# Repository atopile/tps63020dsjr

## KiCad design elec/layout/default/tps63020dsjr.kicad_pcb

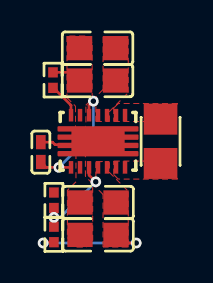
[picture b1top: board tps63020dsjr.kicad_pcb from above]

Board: 2 copper layers, 10 parts (0 on the bottom side), 8 nets.

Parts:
C1, C2, C3, C4: 10µF ±10% 25V X5R; C0805-3b2e55
C5: 100nF ±10% 16V X7R; C0402-b3ef17
L1: 1.5µH ±20% 2.4A 72mΩ; IND-SMD_L2.5-W2.0_WPN252012H-c19fd2
R1: 10kΩ ±1% 62.5mW; R0402-56259e
R2: 26.1kΩ ±1% 62.5mW; R0402-56259e
R3: 1MΩ ±1% 62.5mW; R0402-56259e
U1: VSON-14_L4.0-W3.0-P0.50-BL-EP_TI_DSJ

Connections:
EN: C5.1, U1.1, U1.12
FB: R1.1, R2.2, U1.3
L1: L1.1, U1.8, U1.9
L2: L1.2, U1.6, U1.7
PG: R3.1, U1.14
gnd: C1.2, C2.2, C3.2, C4.2, C5.2, R1.2, R3.2, U1.2, U1.13, U1.15
hv: C1.1, C2.1, U1.10, U1.11
hv-1: C3.1, C4.1, R2.1, U1.4, U1.5

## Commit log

2024-02-16 Configure project
2024-02-17 layout
2024-02-29 updated with equations
2024-03-19 fixing name redefintion for inductor
2024-07-05 Remove crud from layout
2025-01-16 update layout file to latest kicad version, remove the snowman
2025-03-07 Update regulator and passives to library defintions
2025-03-07 Relink layout
2025-03-07 Update ci.yml
    use main to build in CI
